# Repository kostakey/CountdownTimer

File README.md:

# Countdown Timer

## Starting a New Project
[help](https://docs.espressif.com/projects/vscode-esp-idf-extension/en/latest/startproject.html)

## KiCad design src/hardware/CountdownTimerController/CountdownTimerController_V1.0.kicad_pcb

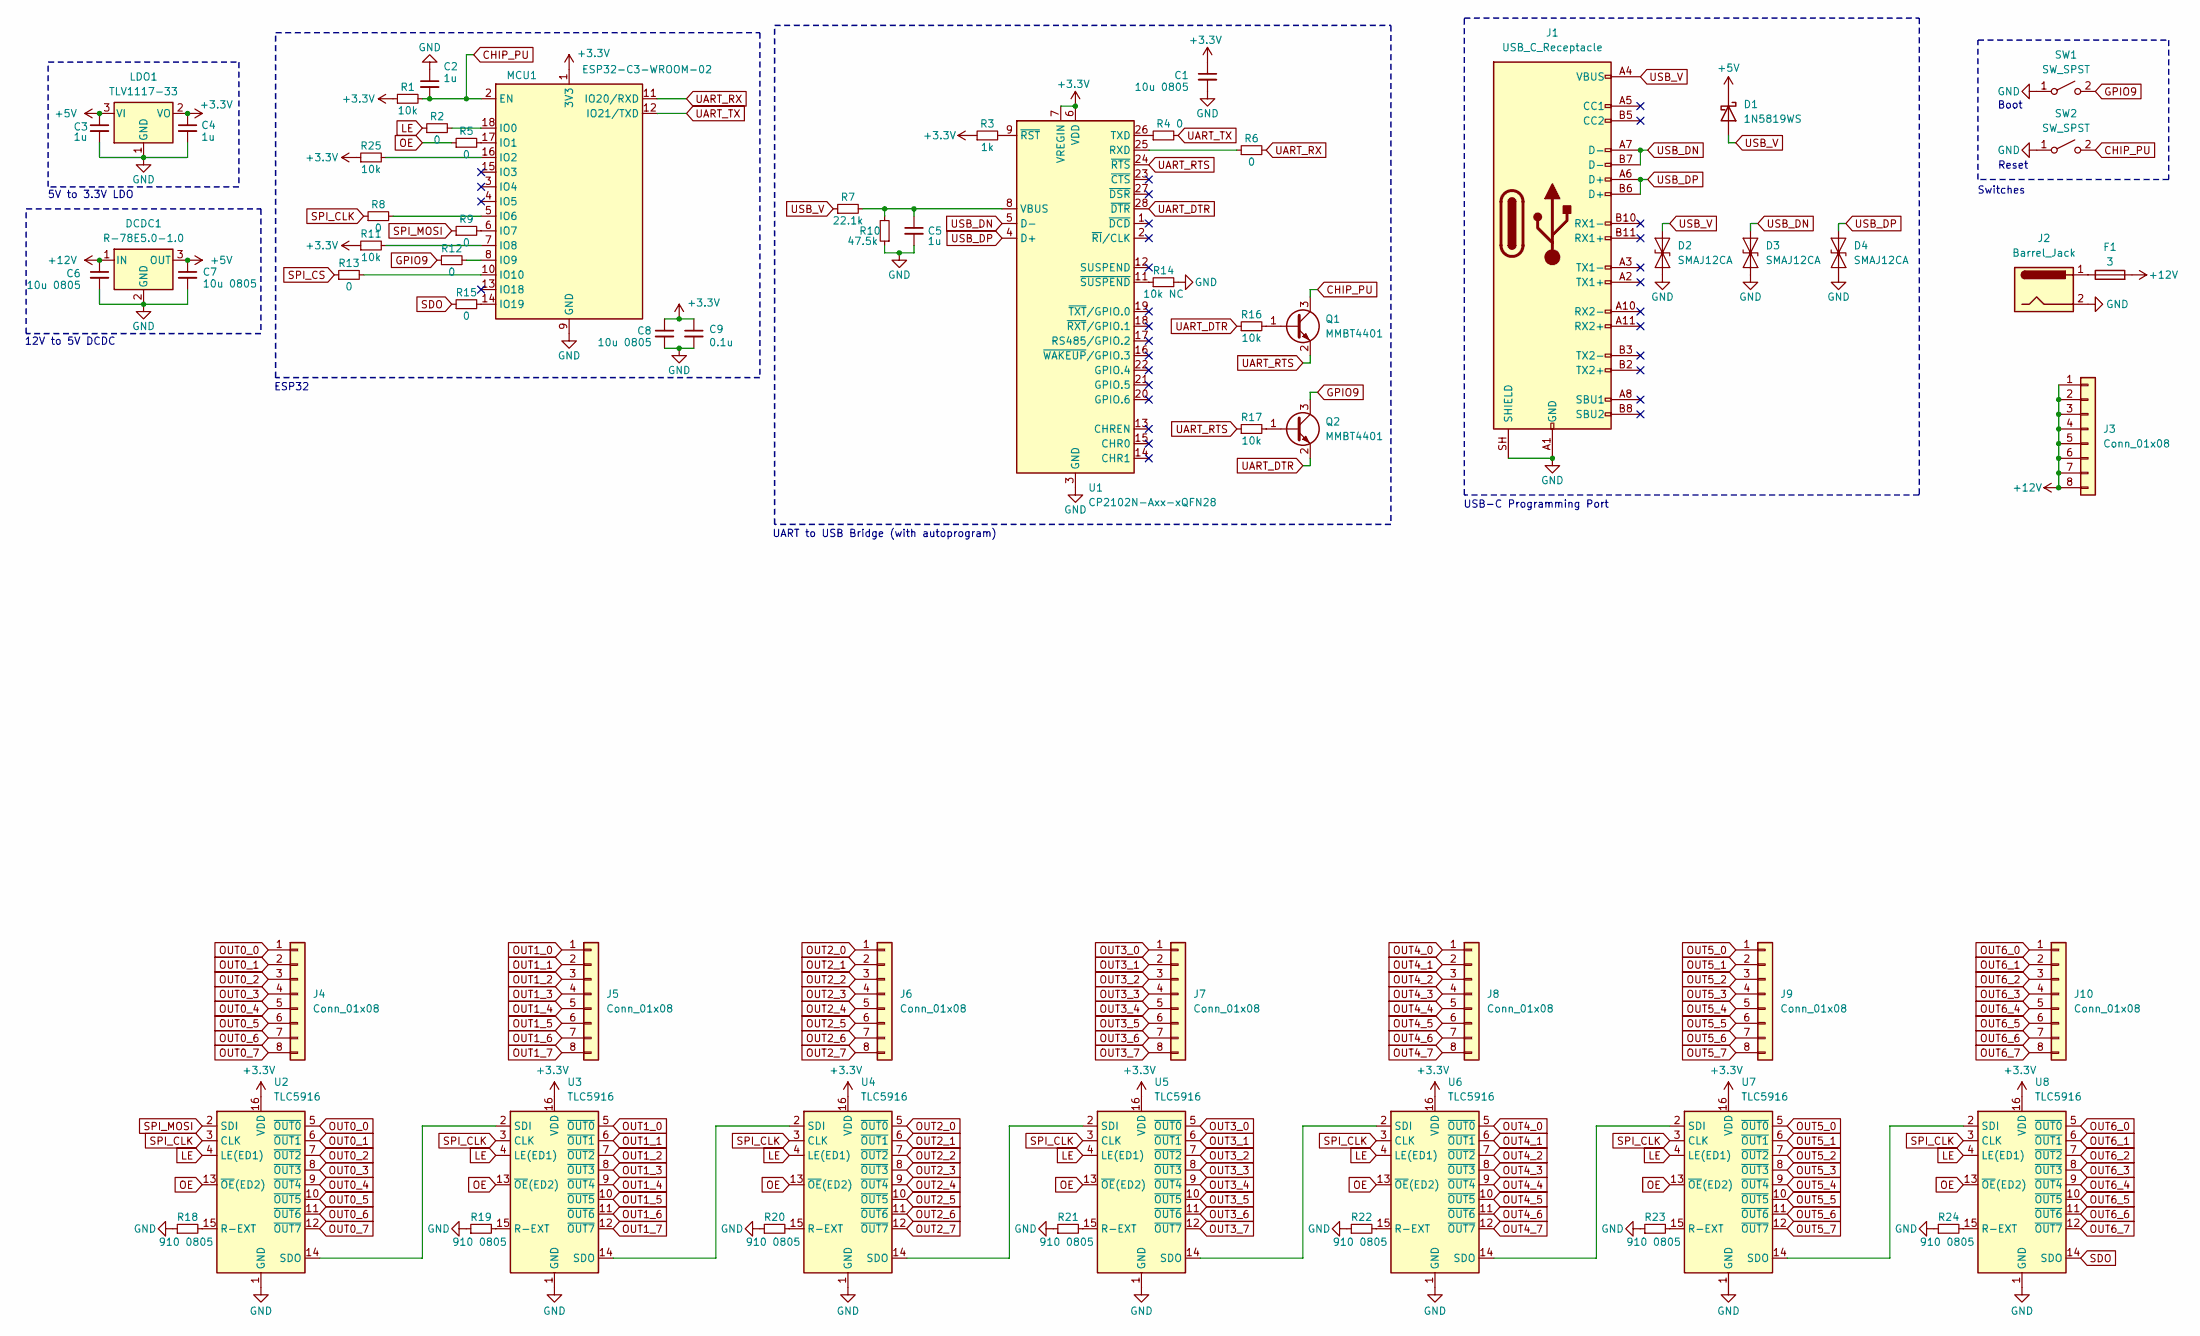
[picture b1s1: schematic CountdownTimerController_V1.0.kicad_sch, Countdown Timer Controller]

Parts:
C1, C6, C7, C8: 10u 0805; C_0805_2012Metric
C2, C3, C4, C5: 1u; C_0603_1608Metric
C9: 0.1u; C_0603_1608Metric
D1: 1N5819WS; D_SOD-123
D2, D3, D4: SMAJ12CA; D_SMA
DCDC1: R-78E5.0-1.0; Converter_DCDC_RECOM_R-78E-0.5_THT
F1: 3; Fuse_0603_1608Metric
J1: USB_C_Receptacle; USB_C_Receptacle_Amphenol_12401610E4-2A
J2: Barrel_Jack; BarrelJack_CUI_PJ-063AH_Horizontal
J3, J4, J5, J6, J7, J8, J9, J10: Conn_01x08; PinHeader_1x08_P2.54mm_Vertical
LDO1: TLV1117-33; SOT-223-3_TabPin2
MCU1: ESP32-C3-WROOM-02
Q1, Q2: MMBT4401; SOT-23
R1, R11, R16, R17, R25: 10k; R_0603_1608Metric
R2, R4, R5, R6, R8, R9, R12, R13, R15: 0; R_0603_1608Metric
R3: 1k; R_0603_1608Metric
R7: 22.1k; R_0603_1608Metric
R10: 47.5k; R_0603_1608Metric
R14: 10k NC; R_0603_1608Metric
R18, R19, R20, R21, R22, R23, R24: 910 0805; R_0805_2012Metric
SW1, SW2: SW_SPST; SW_Push_1P1T_NO_CK_KMR2
U1: CP2102N-Axx-xQFN28; QFN-28-1EP_5x5mm_P0.5mm_EP3.35x3.35mm
U2, U3, U4, U5, U6, U7, U8: TLC5916; SOIC-16_3.9x9.9mm_P1.27mm

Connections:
+3.3V: C1.1, C4.1, C8.1, C9.1, LDO1.2 (VO), MCU1.1 (3V3), R1.1, R3.1, R11.1, R25.1, U1.6 (VDD), U1.7 (VREGIN), U2.16 (VDD), U3.16 (VDD), U4.16 (VDD), U5.16 (VDD), U6.16 (VDD), U7.16 (VDD), U8.16 (VDD)
+5V: C3.1, C7.1, D1.1 (K), DCDC1.3 (OUT), LDO1.3 (VI)
+12V: C6.1, DCDC1.1 (IN), F1.2, J3.1, J3.2, J3.3, J3.4, J3.5, J3.6, J3.7, J3.8
CHIP_PU: C2.2, MCU1.2 (EN), Q1.3 (C), R1.2, SW2.2 (B)
GND: C1.2, C2.1, C3.2, C4.2, C5.2, C6.2, C7.2, C8.2, C9.2, D2.1 (A1), D3.1 (A1), D4.1 (A1), DCDC1.2 (GND), J1.A1 (GND), J1.A12 (GND), J1.B1 (GND), J1.B12 (GND), J1.SH (SHIELD), J2.2, LDO1.1 (GND), MCU1.9 (GND), MCU1.19 (GND), R10.1, R14.2, R18.1, R19.1, R20.1, R21.1, R22.1, R23.1, R24.1, SW1.1 (A), SW2.1 (A), U1.3 (GND), U1.29 (GND), U2.1 (GND), U3.1 (GND), U4.1 (GND), U5.1 (GND), U6.1 (GND), U7.1 (GND), U8.1 (GND)
GPIO9: Q2.3 (C), R12.1, SW1.2 (B)
LE: R2.1, U2.4 (LE(ED1)), U3.4 (LE(ED1)), U4.4 (LE(ED1)), U5.4 (LE(ED1)), U6.4 (LE(ED1)), U7.4 (LE(ED1)), U8.4 (LE(ED1))
unnamed: F1.1, J2.1
unnamed: MCU1.18 (IO0), R2.2
unnamed: MCU1.17 (IO1), R5.2
unnamed: MCU1.16 (IO2), R25.2
unnamed: MCU1.5 (IO6), R8.2
unnamed: MCU1.6 (IO7), R9.2
unnamed: MCU1.7 (IO8), R11.2
unnamed: MCU1.8 (IO9), R12.2
unnamed: MCU1.10 (IO10), R13.2
unnamed: MCU1.14 (IO19), R15.2
unnamed: Q1.1 (B), R16.2
unnamed: Q2.1 (B), R17.2
unnamed: R6.1, U1.25 (RXD)
unnamed: R4.1, U1.26 (TXD)
unnamed: C5.1, R7.2, R10.2, U1.8 (VBUS)
unnamed: R3.2, U1.9 (~RST)
unnamed: R14.1, U1.11 (~SUSPEND)
unnamed: R18.2, U2.15 (R-EXT)
unnamed: U2.14 (SDO), U3.2 (SDI)
unnamed: R19.2, U3.15 (R-EXT)
unnamed: U3.14 (SDO), U4.2 (SDI)
unnamed: R20.2, U4.15 (R-EXT)
unnamed: U4.14 (SDO), U5.2 (SDI)
unnamed: R21.2, U5.15 (R-EXT)
unnamed: U5.14 (SDO), U6.2 (SDI)
unnamed: R22.2, U6.15 (R-EXT)
unnamed: U6.14 (SDO), U7.2 (SDI)
unnamed: R23.2, U7.15 (R-EXT)
unnamed: U7.14 (SDO), U8.2 (SDI)
unnamed: R24.2, U8.15 (R-EXT)
OE: R5.1, U2.13 (~OE(ED2)), U3.13 (~OE(ED2)), U4.13 (~OE(ED2)), U5.13 (~OE(ED2)), U6.13 (~OE(ED2)), U7.13 (~OE(ED2)), U8.13 (~OE(ED2))
OUT0_0: J4.1, U2.5 (~OUT0)
OUT0_1: J4.2, U2.6 (~OUT1)
OUT0_2: J4.3, U2.7 (~OUT2)
OUT0_3: J4.4, U2.8 (~OUT3)
OUT0_4: J4.5, U2.9 (~OUT4)
OUT0_5: J4.6, U2.10 (~OUT5)
OUT0_6: J4.7, U2.11 (~OUT6)
OUT0_7: J4.8, U2.12 (~OUT7)
OUT1_0: J5.1, U3.5 (~OUT0)
OUT1_1: J5.2, U3.6 (~OUT1)
OUT1_2: J5.3, U3.7 (~OUT2)
OUT1_3: J5.4, U3.8 (~OUT3)
OUT1_4: J5.5, U3.9 (~OUT4)
OUT1_5: J5.6, U3.10 (~OUT5)
OUT1_6: J5.7, U3.11 (~OUT6)
OUT1_7: J5.8, U3.12 (~OUT7)
OUT2_0: J6.1, U4.5 (~OUT0)
OUT2_1: J6.2, U4.6 (~OUT1)
OUT2_2: J6.3, U4.7 (~OUT2)
OUT2_3: J6.4, U4.8 (~OUT3)
OUT2_4: J6.5, U4.9 (~OUT4)
OUT2_5: J6.6, U4.10 (~OUT5)
OUT2_6: J6.7, U4.11 (~OUT6)
OUT2_7: J6.8, U4.12 (~OUT7)
OUT3_0: J7.1, U5.5 (~OUT0)
OUT3_1: J7.2, U5.6 (~OUT1)
OUT3_2: J7.3, U5.7 (~OUT2)
OUT3_3: J7.4, U5.8 (~OUT3)
OUT3_4: J7.5, U5.9 (~OUT4)
OUT3_5: J7.6, U5.10 (~OUT5)
OUT3_6: J7.7, U5.11 (~OUT6)
OUT3_7: J7.8, U5.12 (~OUT7)
OUT4_0: J8.1, U6.5 (~OUT0)
OUT4_1: J8.2, U6.6 (~OUT1)
OUT4_2: J8.3, U6.7 (~OUT2)
OUT4_3: J8.4, U6.8 (~OUT3)
OUT4_4: J8.5, U6.9 (~OUT4)
OUT4_5: J8.6, U6.10 (~OUT5)
OUT4_6: J8.7, U6.11 (~OUT6)
OUT4_7: J8.8, U6.12 (~OUT7)
OUT5_0: J9.1, U7.5 (~OUT0)
OUT5_1: J9.2, U7.6 (~OUT1)
OUT5_2: J9.3, U7.7 (~OUT2)
OUT5_3: J9.4, U7.8 (~OUT3)
OUT5_4: J9.5, U7.9 (~OUT4)
OUT5_5: J9.6, U7.10 (~OUT5)
OUT5_6: J9.7, U7.11 (~OUT6)
OUT5_7: J9.8, U7.12 (~OUT7)
OUT6_0: J10.1, U8.5 (~OUT0)
OUT6_1: J10.2, U8.6 (~OUT1)
OUT6_2: J10.3, U8.7 (~OUT2)
OUT6_3: J10.4, U8.8 (~OUT3)
OUT6_4: J10.5, U8.9 (~OUT4)
OUT6_5: J10.6, U8.10 (~OUT5)
OUT6_6: J10.7, U8.11 (~OUT6)
OUT6_7: J10.8, U8.12 (~OUT7)
SDO: R15.1, U8.14 (SDO)
SPI_CLK: R8.1, U2.3 (CLK), U3.3 (CLK), U4.3 (CLK), U5.3 (CLK), U6.3 (CLK), U7.3 (CLK), U8.3 (CLK)
SPI_CS: R13.1
SPI_MOSI: R9.1, U2.2 (SDI)
UART_DTR: Q2.2 (E), R16.1, U1.28 (~DTR)
UART_RTS: Q1.2 (E), R17.1, U1.24 (~RTS)
UART_RX: MCU1.11 (IO20/RXD), R6.2
UART_TX: MCU1.12 (IO21/TXD), R4.2
USB_DN: D3.2 (A2), J1.A7 (D-), J1.B7 (D-), U1.5 (D-)
USB_DP: D4.2 (A2), J1.A6 (D+), J1.B6 (D+), U1.4 (D+)
USB_V: D1.2 (A), D2.2 (A2), J1.A4 (VBUS), J1.A9 (VBUS), J1.B4 (VBUS), J1.B9 (VBUS), R7.1

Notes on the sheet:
12V to 5V DCDC
Reset
Boot
5V to 3.3V LDO
ESP32
Switches
USB-C Programming Port
UART to USB Bridge (with autoprogram)

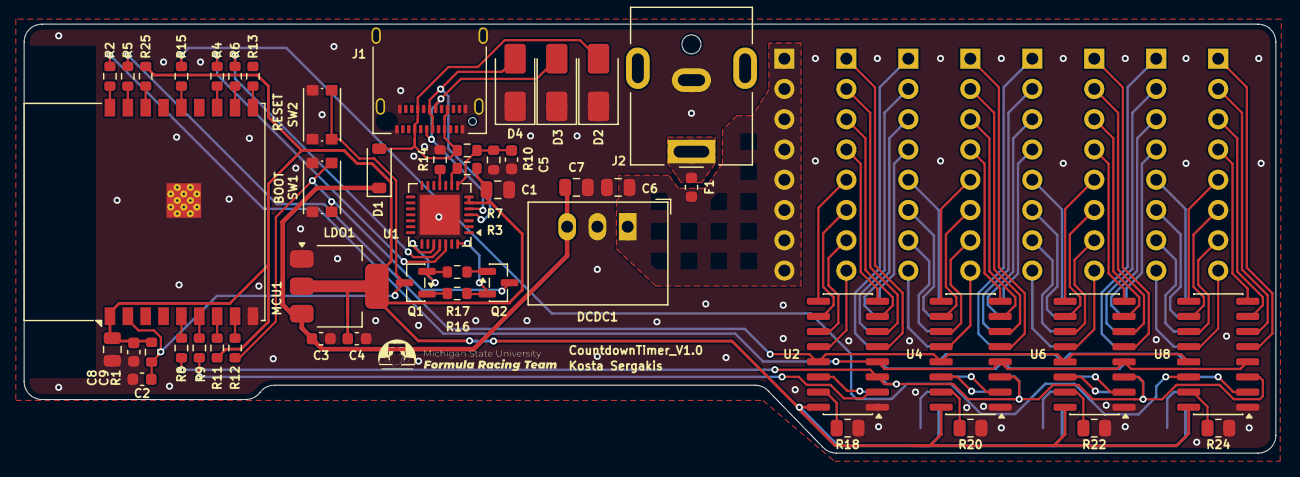
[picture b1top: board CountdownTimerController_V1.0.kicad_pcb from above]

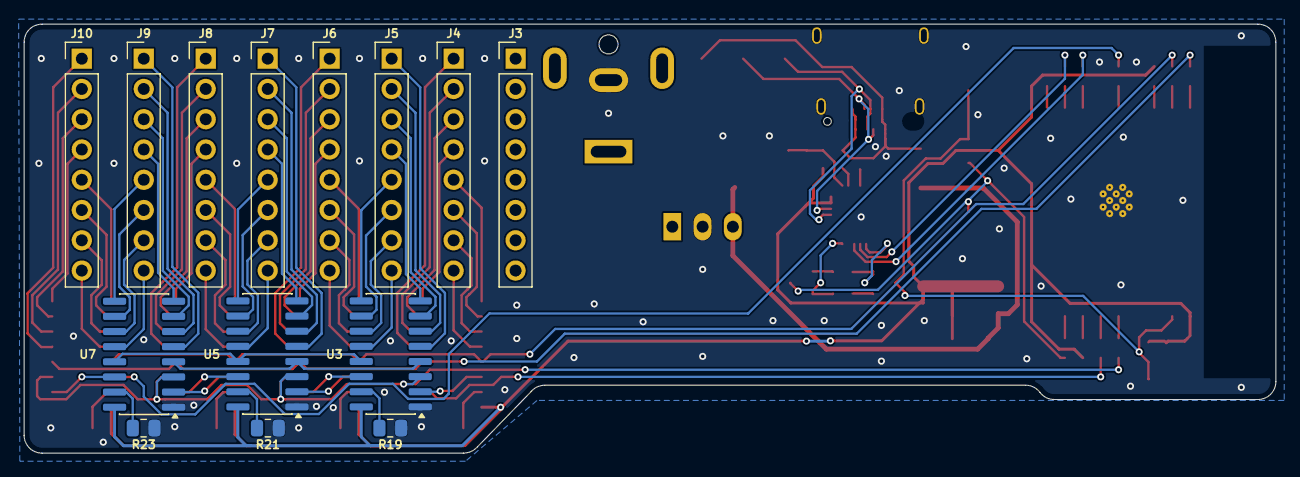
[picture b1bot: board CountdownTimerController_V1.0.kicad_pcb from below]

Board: 2 copper layers, 105.0 x 36.0 mm, 64 parts (14 on the bottom side), 104 nets.

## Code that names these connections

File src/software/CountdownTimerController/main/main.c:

#include <stdio.h>

// FreeRTOS things 
#include "freertos/FreeRTOS.h"
#include "freertos/task.h"

// GPIO
#include "driver/gpio.h"

// PWM things
#include "driver/ledc.h"

// SPI
#include "driver/spi_master.h"

// more
#include "esp_log.h"

// TLC5916 pin definitions
#define LE_PIN 0 // latch enable (treat as spi cs)
#define OE_PIN 1 // output enable for pwm brightness control (active low)
#define SDO_PIN 19

// SPI pin definitions
#define SPI_CLK_PIN 6
#define SPI_MOSI_PIN 7
#define SPI_MISO_PIN -1 // unused
#define SPI_CS_PIN -1 // unused

// System config
#define NUM_TLC5916 7 // number of tlc5916 chips on spi bus
#define TOTAL_BYTES NUM_TLC5916 // 1 tlc5916 = 1 byte

spi_device_handle_t spi_device;

void init_tlc5916(void){

    // configure the spi bus
    spi_bus_config_t buscfg = {
        .miso_io_num        = SPI_MISO_PIN,
        .mosi_io_num        = SPI_MOSI_PIN,
        .sclk_io_num        = SPI_CLK_PIN,
        .quadwp_io_num      = -1,
        .quadhd_io_num      = -1,
        .max_transfer_sz    = 64
    };
    ESP_ERROR_CHECK(spi_bus_initialize(SPI2_HOST, &buscfg, SPI_DMA_CH_AUTO));

    // configure the spi device
    spi_device_interface_config_t devcfg = {
        .clock_speed_hz     = 1000000, // 1MHz, double check tlc capability
        .mode               = 0,
        .spics_io_num       = LE_PIN,
        .queue_size         = 1,
        .flags              = SPI_DEVICE_NO_DUMMY,
    };
    ESP_ERROR_CHECK(spi_bus_add_device(SPI2_HOST, &devcfg, &spi_device));

    // configure pwm timer
    ledc_timer_config_t ledc_timer = {
        .speed_mode         = LEDC_LOW_SPEED_MODE,
        .timer_num          = LEDC_TIMER_0,
        .duty_resolution    = LEDC_TIMER_8_BIT, // duty cycle range from 0 to 255
        .freq_hz            = 5000, // 5kHz
        .clk_cfg            = LEDC_AUTO_CLK
    };
    ESP_ERROR_CHECK(ledc_timer_config(&ledc_timer));

    // configure pwm channel
    ledc_channel_config_t ledc_channel = {
        .speed_mode = LEDC_LOW_SPEED_MODE,
        .channel    = LEDC_CHANNEL_0,
        .timer_sel  = LEDC_TIMER_0,
        .intr_type  = LEDC_INTR_DISABLE,
        .gpio_num   = OE_PIN,
        .duty       = 0, // 0 = full brightness since pin is active low
        .hpoint     = 0,
    };
    ESP_ERROR_CHECK(ledc_channel_config(&ledc_channel));
}

void set_brightness(uint8_t brightness){
    // oe is active low, need to invert duty value
    uint32_t duty = 255 - brightness;
    
    ESP_ERROR_CHECK(ledc_set_duty(LEDC_LOW_SPEED_MODE, LEDC_CHANNEL_0, duty));
    ESP_ERROR_CHECK(ledc_update_duty(LEDC_LOW_SPEED_MODE, LEDC_CHANNEL_0));
}

void update_tlc5916(uint8_t *data_buffer){
    spi_transaction_t t;
    memset(&t, 0, sizeof(t));

    t.length = TOTAL_BYTES * 8; // 7 bytes * 8 bits = 56 bits
    t.tx_buffer = data_buffer;
    t.rx_buffer = NULL;

    ESP_ERROR_CHECK(spi_device_transmit(spi_device, &t));
}

void app_main(void){

    init_tlc5916();

    // tx_data[0] = Chip 7 (end of chain)
    // tx_data[6] = Chip 1 (directly connected to ESP32 MOSI)
    uint8_t tx_data[TOTAL_BYTES] = {0};

    // Turn all 56 outputs ON for the demo
    memset(tx_data, 0xFF, TOTAL_BYTES);
    update_tlc5916(tx_data);

    while(1){
        
        // fade up from dim to full brightness
        for (int b = 0; b <= 255; b++) {
            set_brightness(b);
            vTaskDelay(pdMS_TO_TICKS(10));
        }

        // fade down from bright to dim
        for (int b = 255; b >= 0; b--) {
            set_brightness(b);
            vTaskDelay(pdMS_TO_TICKS(10));
        }

        // delay
        vTaskDelay(pdMS_TO_TICKS(500));
    }

}

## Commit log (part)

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2026-06-29 hardware
